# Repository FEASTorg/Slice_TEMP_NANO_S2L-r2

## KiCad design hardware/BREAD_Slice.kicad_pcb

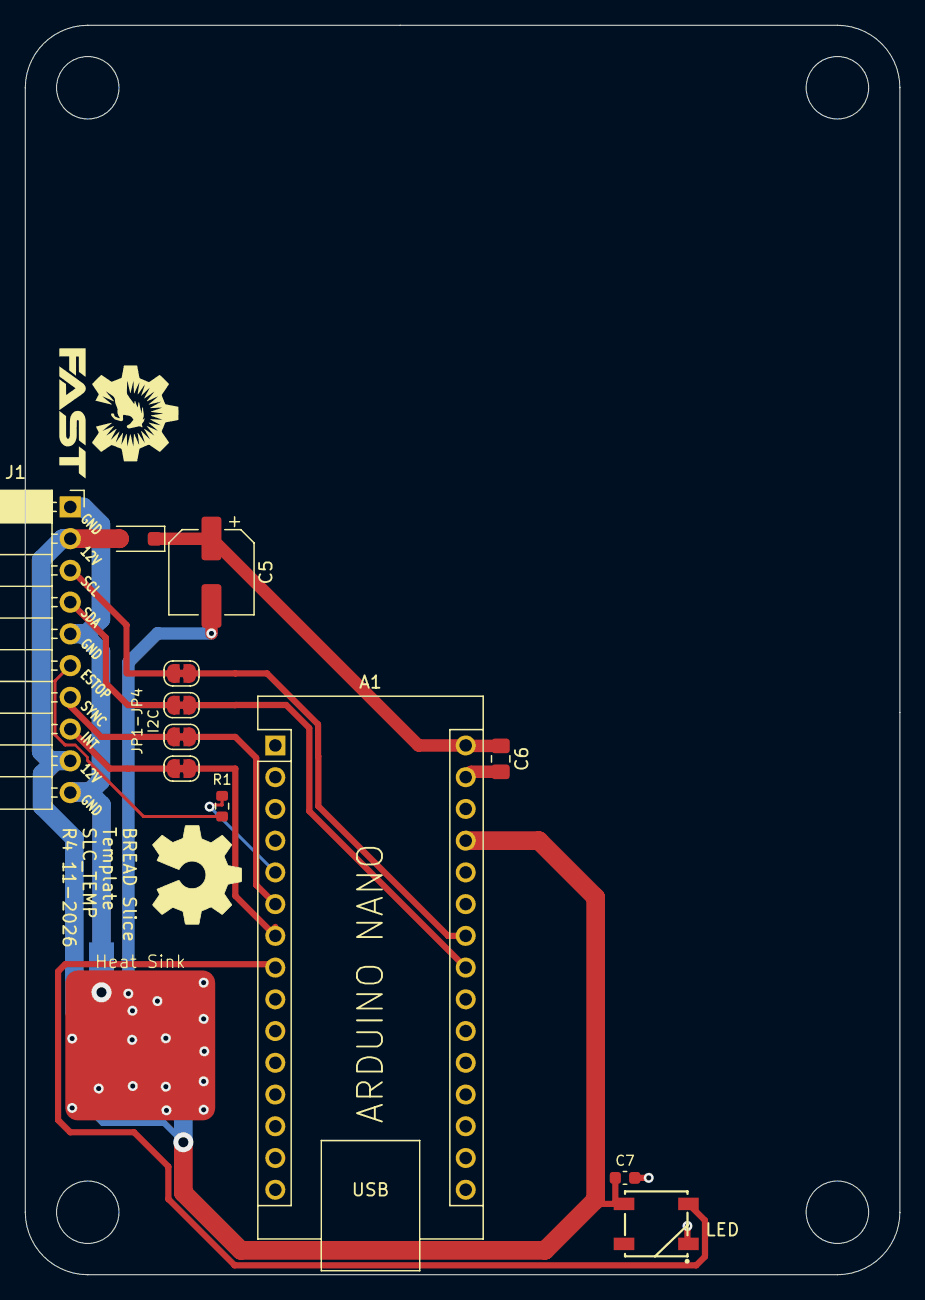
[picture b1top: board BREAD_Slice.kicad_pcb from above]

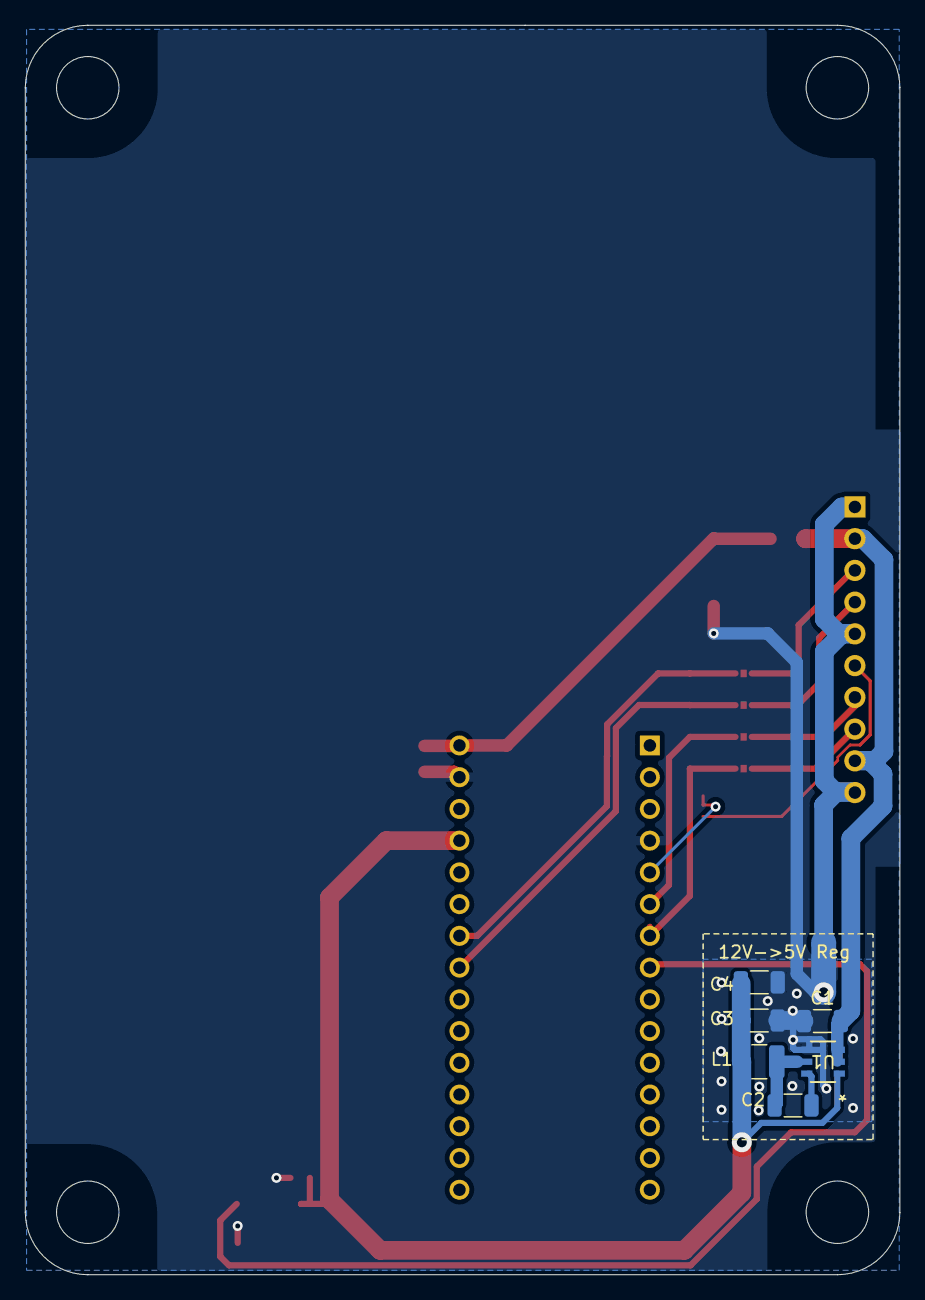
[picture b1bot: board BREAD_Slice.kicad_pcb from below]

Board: 2 copper layers, 70.0 x 100.0 mm, 25 parts (7 on the bottom side), 18 nets.

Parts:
A1: Arduino_Nano_v3.x; Arduino_Nano_Headers
C1: 10u 25V; C_1206_3216Metric
C2: 100nF; C_1206_3216Metric
C3, C4: 22u 10V; C_1206_3216Metric
C5: 47u 25V; CP_Elec_6.3x7.7
C6: 0.1u; C_0805_2012Metric_Pad1.18x1.45mm_HandSolder
C7: 100n; C_0603_1608Metric
D1: SM4007PL; D_SOD-123F
D2: WS2812B_5050; WS2812-5050-4PIN
H1, H2, H3, H4: MountingHole; MountingHole_5mm
HS1: Heatsink_Pad; Thermal_Pad
J1: Conn_01x10_Socket; PinSocket_1x10_P2.54mm_Horizontal
JP1: I2C_CLK bus link; SolderJumper-2_P1.3mm_Bridged_RoundedPad1.0x1.5mm
JP2: I2C_DAT bus link; SolderJumper-2_P1.3mm_Bridged_RoundedPad1.0x1.5mm
JP3: SYNC bus link; SolderJumper-2_P1.3mm_Bridged_RoundedPad1.0x1.5mm
JP4: INT bus link; SolderJumper-2_P1.3mm_Bridged_RoundedPad1.0x1.5mm
L1: 4.7uH Isat>=1.4A; L_1210_3225Metric
NT1: NetTie_2; NetTie-2_SMD_Pad2.0mm
R1: 1k; R_0603_1608Metric
Ref**: Val**; OSHW_Logo_8mm
U1: AP63205; SOIC_05WU-7_DIO

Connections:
+5V: A1.27 (+5V), C3.2, C4.2, C7.1, D2.1 (VDD), L1.2, U1.1 (FB)
+12V: C1.2, D1.2 (A), J1.2, J1.9, U1.2 (EN), U1.3 (VIN)
/slice_template/ESTOP: J1.6, R1.1
/slice_template/I2C_CLK: J1.3, JP1.1
/slice_template/I2C_CLK/A5: A1.24 (A5), JP1.2
/slice_template/I2C_DAT: J1.4, JP2.1
/slice_template/I2C_DAT/A4: A1.23 (A4), JP2.2
/slice_template/INT: J1.8, JP4.1
/slice_template/INT/CAN_{CS}: A1.7 (D4), JP4.2
/slice_template/LED: A1.8 (D5), D2.4 (DIN)
/slice_template/SYNC: J1.7, JP3.1
/slice_template/SYNC/CAN_{INT}: A1.6 (D3), JP3.2
/slice_template/VIN: A1.30 (VIN), C5.1, C6.1, D1.1 (K)
GND: A1.4 (GND), A1.29 (GND), C1.1, C3.1, C4.1, C5.2, C6.2, C7.2, D2.3 (VSS), HS1.1, NT1.1, U1.4 (GND)
GNDPWR: J1.1, J1.5, J1.10, NT1.2
unnamed: A1.5 (D2), R1.2
unnamed: C2.2, U1.6 (BST)
unnamed: C2.1, L1.1, U1.5 (SW)

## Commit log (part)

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2025-09-24 initial commit post-fork to r2
2025-09-24 ci: remove old repeated push terms to trigger wf
2025-09-24 add configs and remove nucleo assets
2025-09-24 📄 KiBot index + board renders (auto)
2025-09-24 update readme and autpsave
2025-09-24 update references to TEMP
2026-01-26 update gitignore
2026-04-20 refactor: org casing rename from 'FEASTorg' to 'feastorg'
2026-05-20 Add slice.yaml manifest (schema v1.0)
2026-05-24 Add standardized TODO.md with Pass 1/Pass 2 structure
